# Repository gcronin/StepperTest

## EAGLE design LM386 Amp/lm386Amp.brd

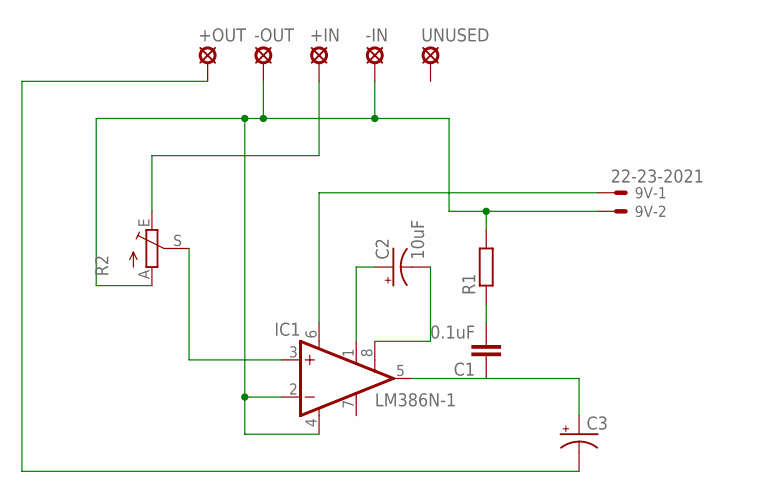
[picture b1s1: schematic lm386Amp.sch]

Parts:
9V: 22-23-2021
+IN: LSP10
+OUT: LSP10
-IN: LSP10
-OUT: LSP10
C1: 0.1uF; C5B3
C2: 10uF; B45181B
C3: CAP_POLPTH4; CPOL-RADIAL-1000UF-25V
IC1: LM386N-1; DIL08
R1: R0204/7; 0204/7
R2: TRIM_EU-CA14H; CA14H
UNUSED: LSP10

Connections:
GND: 9V.2, -IN.MP, -OUT.MP, IC1.2 (-IN), IC1.4 (GND), R1.2, R2.A
unnamed: C2.+, IC1.1 (GAIN)
unnamed: C2.-, IC1.8 (GAIN)
unnamed: 9V.1, IC1.6 (VS)
unnamed: C1.1, C3.1 (+), IC1.5 (OUT)
unnamed: +IN.MP, R2.E
unnamed: IC1.3 (+IN), R2.S
unnamed: C1.2, R1.1
unnamed: +OUT.MP, C3.2 (-)

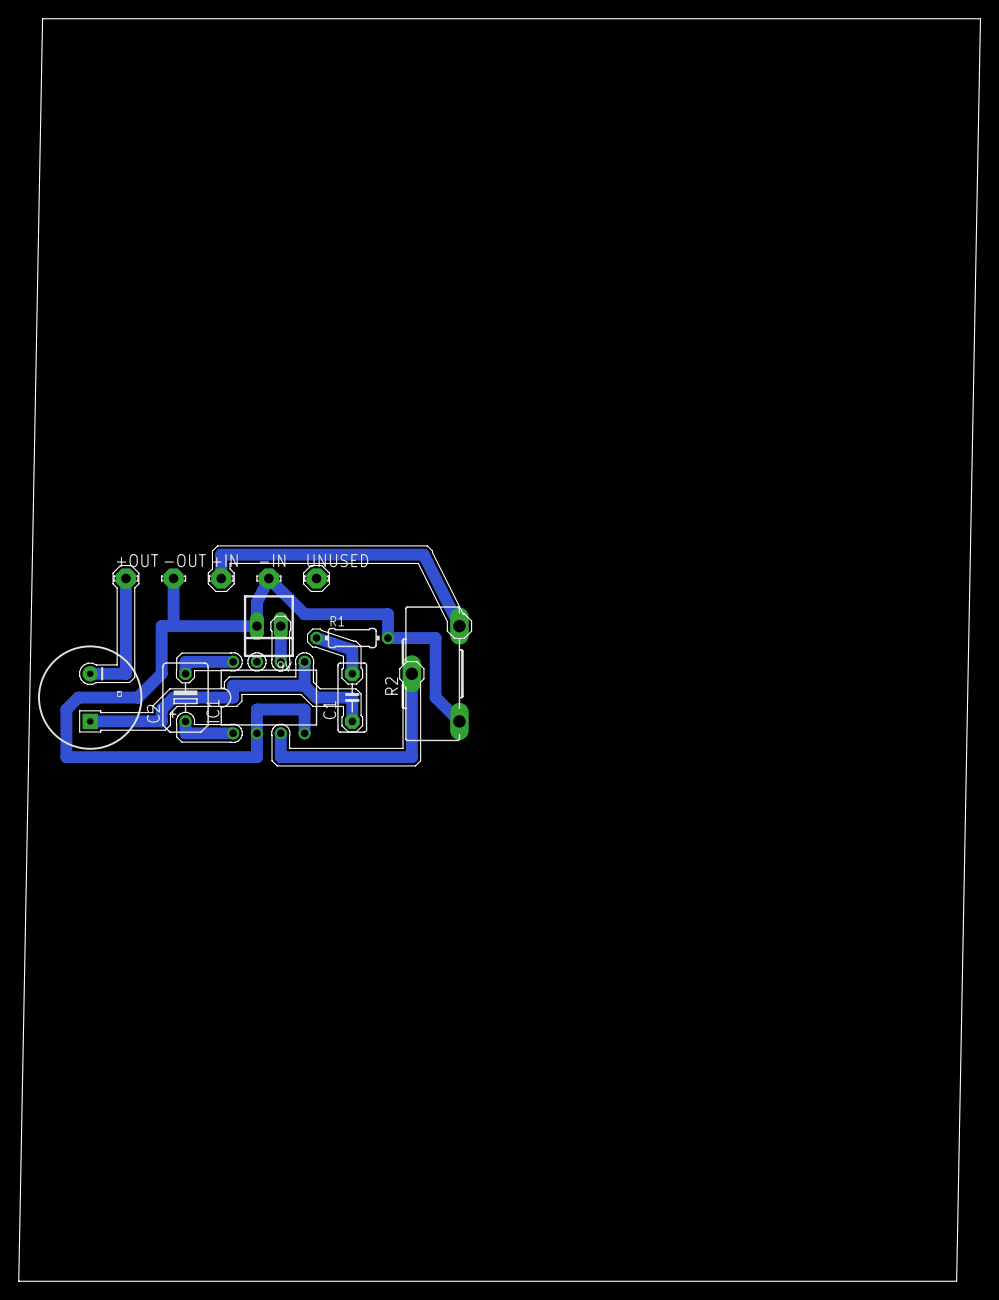
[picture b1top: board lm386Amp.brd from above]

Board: 2 copper layers, 102.5 x 134.6 mm, 12 parts (0 on the bottom side), 9 nets.

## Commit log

2013-04-08 Single Stepper motor for PSMD Triple Axis Board
    Single Step every second
2013-04-11 StepperTest: added 2nd motor, added reading of xmax to change direction or enable/disable steppers
    Initial Commit for Ethernet Based Code: Incorpates Webpage to Control
    Direction & #Degrees of two motors. Interweaves stepper motion so both
    move at the same time. Not calibrated.
2013-04-11 Second Motor Added/Xmax Read
    Xmax controls direction or enable/disable.
2013-04-28 Working Version after Physical Build
    Ethernet:
    - Variables into Arrays
    - Consolidated Functions into one per instance
    - Added functions to split different tasks
    Single Stepper
    - Added actual pins
2013-04-28 LimitSwitches, Home Position at Startup
    Tested, Works
2013-04-28 Cumulative Steps Added
    Fixed Interweave Bug, added Cumulative Steps taken in X/Y Directions,
    Displayed these on HTML page
2013-04-28 Center Position added, Move Boundaries Added
    Also removed the "degrees" and am in steps now...
2013-05-03 Processing Controlling Arduino over Serial: Initial Commit
    Need to Fix Directions in Arduino Sketch... Need to Pass 4 bytes for
    direction/distance for X/Y
2013-05-03 Untested: Fix Cumulative Steps Bug in Find Center and Find Home Position
    Directions were not being set and were still 0, so Increment Cumulative Step function did not work.
2013-05-03 Processing Added Platform Grid
    also buttons for limit switches
2013-05-05 Processing -> Added send Bytes to Arduino,
    Tested... does work but weird motions for Arduino... need to check that
    correct values are being received by Arduino, and need to check the
    "moveToPosition" and "center" functions .
    Arduino... receives bytes from Processing. Also fixed "abs" bug in
    "center" and "MovetoPosition" functions.
2013-05-07 Arduino fix ABS bug, send location to Processing
    Arduino: Fixed ABS bug with moveXY, checkMove uses local variables,
    sends Xcoor and Ycoor to Processing (debug), added moveToPosition
    function, stepper actions only happen if steppers enabled, and
    moveToPosition only happens if center/home isn't happening
2013-05-08 Working Version!!!!
    Arduino: OutputString moved after stepper action is done, interweave
    bug fixed
2013-05-26 Implemented Jog Mode
    Arduino: note "currentDirectionZ" bug fixed
    Processing: added buttons
2013-06-04 PenUp/Down Added, LimitSwitches Fixed
    Also, Z axis zero is reset by pressing limit switch
2013-07-30 Frostruder Added
2013-08-02 Frosting On/Off with Pen Up/Down
    Tested, works
2013-08-12 New Interweave
    Fixes problem of slope change
2013-08-14 Arduino: Fix Up/Down Bug Processing: Add Cookies/Clear
2013-08-15 Arduino: Fixed >= Bug, Switched Extruder Pins, Decreased Step Speed
2016-11-07 Sketch to Run 1 Stepper + Star Spangled Banner
2016-12-06 Added PCB files for LM386 Board

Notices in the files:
parts and their libraries:
SparkFun: Licensing: CC v3.0 Share-Alike You are welcome to use this library for commercial purposes.
